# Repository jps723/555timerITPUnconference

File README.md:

# 555timer ITPUnconference Materials

Files required as a part of an introductory workshop on Eagle and use of the Othermill.  

Initially led on 1/26/19 at ITP/NYU.

[Slides](https://docs.google.com/presentation/d/13K9FViqeBvbfOR0MSYSRqEZHbCwhsgrEbNn7OOyvbPI/edit#slide=id.g4dbb07c922_0_12)

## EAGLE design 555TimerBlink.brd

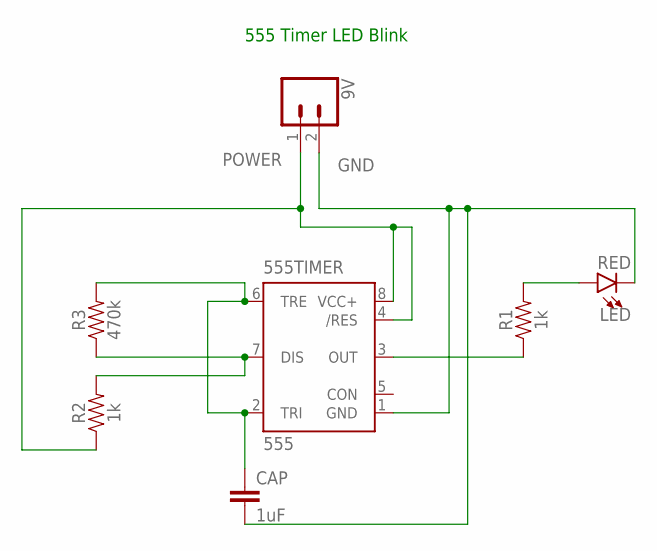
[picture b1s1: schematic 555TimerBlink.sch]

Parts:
9V: CONN_02; 1X02
555TIMER: 555; DIP08-KIT
CAP: 1uF; CAP-PTH-10MM
LED: RED; LED_3MM-NS
R1, R2: 1k; AXIAL-0.3
R3: 470k; AXIAL-0.3

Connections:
GND: 9V.2, 555TIMER.1 (GND), CAP.2, LED.K (C)
unnamed: 555TIMER.2 (TRI), 555TIMER.6 (TRE), CAP.1, R3.P$2 (2)
unnamed: 555TIMER.7 (DIS), R2.P$2 (2), R3.P$1 (1)
unnamed: 555TIMER.3 (OUT), R1.P$1 (1)
unnamed: LED.A, R1.P$2 (2)
POWER: 9V.1, 555TIMER.4 (/RES), 555TIMER.8 (VCC+), R2.P$1 (1)

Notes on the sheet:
555 Timer LED Blink

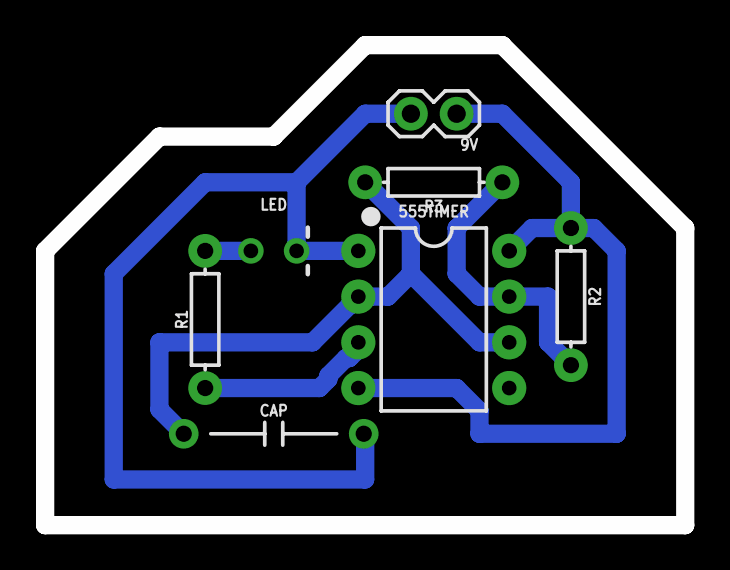
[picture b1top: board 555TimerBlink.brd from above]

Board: 2 copper layers, 35.6 x 26.7 mm, 7 parts (0 on the bottom side), 6 nets.

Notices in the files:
parts and their libraries:
SparkFun-Connectors: Licensing: Creative Commons ShareAlike 4.0 International - https://creativecommons.org/licenses/by-sa/4.0
